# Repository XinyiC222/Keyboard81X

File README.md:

# Keyboard81X WORK IN PROGRESS

A custom 75% PCB keyboard with a rotary encoder and 81 keys.

## Build Notes

- PCB was designed in **KiCad** using a keyswitch plugin.
  - If you are trying to find it here are the ones I used:
    - **KLE Placer**  /Organize the keys and diodes automatically based on .json file
    - **JLCPCB tools** / used for BOM and Placement for JLC pcbs (**EDIT**: New version does not use JLCPCB assembly so this tool was no longer used in the final version. But this tool really do come in handy!)
- Case was modeled in **Fusion**.
## Tools I used
- Plate was generated with: <http://builder.swillkb.com/>
- Keyboard Layout Editor: <https://www.keyboard-layout-editor.com/>
- Keycaps used in the model: <https://github.com/anhthang/dsa-keycap>
- Footprint Library I used in Kicad: <https://github.com/daprice/keyswitches.pretty>

## How To Build Your Own! <h3>PCB</h3>

1. Build your layout with the layout editor I mentioned in the tools I used.
2. Download the .json file from there.
3. In KiCad schematics choose your microcontroller or just use a chip. I used a **Raspberry Pi Pico** for the final version and placed it under the space bar. Other option: you could use a RP2040 chip and build somewhat of a dev board inside the project. That includes the Flash Memory to store the code, Crystal Oscillator (it's like the conductor), USB for power with a voltage regulator, and some capacitors.
4. Then add the current amount of MX_SW_HS you need based on the layout you made.
5. Add the same amount of diodes so each key has one that includes any rotary encoders.
6. Then after that you can add some MX_Stab for the ones you want to stabilize. Some keys like the spacebar need stabilizers, so you can change them to different footprints from the other keys. If you decided to use plate mounted stabilizers instead, you can leave this part out, otherwise if you're using pcb mounted stabilizers then you should add MX_Stab.
7. Add footprint to all your components and don't forget to **Annotate the entire Schematics**
8. Now when designing the PCB, using the .json file and the KLE Placer plugin, you can easily place them all accordingly.
9. Remember to add a border around to create the edge of the PCB in the Edge.cut layer.
10. Organize all the components to your liking and route all of them to each other.
11. **Generate the Gerber Files!**
12. Then if you were to use JLCPCB assembly, you can use the JLCPCB tools to find all the components and create the correct BOM and CPL.
13. You can then upload those files into JLCPCB and order from there!!

<h3>Case</h3>

1. Go into Fusion and create a new project.
2. Download the 3D view of your keyboard from KiCad and upload it (for reference!)
3. Then make the case around it any way you like. If you are 3D printing remember that prints can shrink so you need to **account for tolerances especially holes**
4. you can add a plate and any type of mounting you want
5. If you are adding a plate, the plate generator I included above might be helpful
6. For the plate if you are 3D printing with PLA, having it at 1.5mm thick is usually not strong enough. Set it to **3mm** but leave the area around the stabilizers to be 1.5mm. Note that **prioritizing stability would cause your switches to not clip on correctly**, but will still be tight enough to hold them.

<h3>That's pretty much a good summary of how to build your own keyboard! Thanks for reading it and I hope you learned something new. This is my first big project and definitely my first keyboard build so I don't expect everything to be correct. So if you are building this based off of mine, it's not guaranteed to work. Have fun!!</h3>

## Schematics

## PCB

## BOM
Everything under quantity is the amount you need but the links you buy them come in bulk so they give you more than what you need.

| Item | Purpose | Price | Quantity | Source |
| --- | --- | --- | --- | --- |
| Raspberry Pi Pico | Mirco-controller | $1.99 | 1 | [Aliexpress](https://www.aliexpress.com/item/3256807207612469.html?spm=a2g0o.cart.0.0.6ac438dadamcUQ&mp=1&sourceType=570&pdp_npi=6%40dis%21USD%21USD%208.66%21USD%202.39%21%21USD%201.98%21%21%21%402101d3fe17861144495612456e0f9a%2112000040565295947%21ct%21US%217294405090%21%211%210%21&pdp_ext_f=%7B%22cart2PdpParams%22%3A%7B%22sourceType%22%3A%22570%22%2C%22cartSource%22%3A%22main%22%7D%7D) |
| 1N5817 DO-41 | USB_C VBUS | $1.79 | x1 | [Aliexpress](https://www.aliexpress.com/item/3256809192784213.html?spm=a2g0o.cart.0.0.6ac438dadamcUQ&mp=1&pdp_npi=6%40dis%21USD%21USD%203.83%21USD%201.92%21%21USD%201.92%21%21%21%402103119c17861142221435145e2191%2112000048926087942%21ct%21US%217294405090%21%211%210%21) |
| Keycaps | for the Keys | $4.73 | x80 | [Aliexpress](https://www.aliexpress.com/item/3256808108935624.html?spm=a2g0o.cart.0.0.6ac438dadamcUQ&mp=1&pdp_npi=6%40dis%21USD%21USD%204.73%21USD%204.73%21%21USD%204.73%21%21%21%402103119c17861142221435145e2191%2112000044523183095%21ct%21US%217294405090%21%211%210%21) |
| Plate Mounted Stabilizers | stab for space bar etc | $2.99 | has one 6.25u and two 2u | [Aliexpress](https://www.aliexpress.com/item/3256808467378574.html?spm=a2g0o.cart.0.0.6ac438dadamcUQ&mp=1&sourceType=570&pdp_npi=6%40dis%21USD%21USD%203.32%21USD%202.99%21%21USD%202.47%21%21%21%402101d3fe17861144495612456e0f9a%2112000046108045634%21ct%21US%217294405090%21%211%210%21&pdp_ext_f=%7B%22cart2PdpParams%22%3A%7B%22sourceType%22%3A%22570%22%2C%22cartSource%22%3A%22main%22%7D%7D) |
| SMD turtle switches | Reset button | $2.19 | x1 | [Aliexpress](https://www.aliexpress.com/item/3256805092773328.html?spm=a2g0o.cart.0.0.6ac438dadamcUQ&mp=1&sourceType=570&pdp_npi=6%40dis%21USD%21USD%202.25%21USD%202.19%21%21USD%201.81%21%21%21%402101d3fe17861144495612456e0f9a%2112000032466018228%21ct%21US%217294405090%21%211%210%21&pdp_ext_f=%7B%22cart2PdpParams%22%3A%7B%22sourceType%22%3A%22570%22%2C%22cartSource%22%3A%22main%22%7D%7D) |
| Hot Swap Sockets | hot swap keys | $6.20 | x80 | [Aliexpress](https://www.aliexpress.com/item/3256809001206372.html?spm=a2g0o.cart.0.0.6ac438dadamcUQ&mp=1&pdp_npi=6%40dis%21USD%21USD%2017.45%21USD%206.20%21%21USD%206.20%21%21%21%402101d3fe17861144435192279e0f9a%2112000048235529402%21ct%21US%217294405090%21%211%210%21) |
| Silent Axis switch | switches | $7.66 | x80 | [Aliexpress](https://www.aliexpress.com/item/3256812192263951.html?spm=a2g0o.cart.0.0.6ac438dadamcUQ&mp=1&pdp_npi=6%40dis%21USD%21USD%2018.05%21USD%207.66%21%21USD%207.66%21%21%21%402103119c17861142221435145e2191%2112000058235272628%21ct%21US%217294405090%21%211%210%21) |
| Type C Female | PCB for power | $2.24 | x1 | [Aliexpress](https://www.aliexpress.com/item/3256804989275660.html?spm=a2g0o.cart.0.0.6ac438dadamcUQ&mp=1&pdp_npi=6%40dis%21USD%21USD%202.27%21USD%202.26%21%21USD%202.26%21%21%21%402101d3fe17861144455232342e0f9a%2112000031972190842%21ct%21US%217294405090%21%211%210%21) |
| Solder | soldering | $2.14 | x1 | [Aliexpress](https://www.aliexpress.com/item/3256812349220377.html?spm=a2g0o.cart.0.0.6ac438dadamcUQ&mp=1&pdp_npi=6%40dis%21USD%21USD%204.45%21USD%202.14%21%21USD%202.14%21%21%21%402103119c17861142221435145e2191%2112000058646043574%21ct%21US%217294405090%21%211%210%21) |
| 5.1k resistors | for ground near usb-c | $2.48 | x2 | [Aliexpress](https://www.aliexpress.com/item/3256811592848349.html?spm=a2g0o.cart.0.0.6ac438dadamcUQ&mp=1&pdp_npi=6%40dis%21USD%21USD%203.01%21USD%202.42%21%21USD%202.42%21%21%21%402103119c17861142221435145e2191%2112000056534710480%21ct%21US%217294405090%21%211%210%21) |
| IN4148 DO-35 | matrix | $1.92 | x81 | [Aliexpress](https://www.aliexpress.com/item/3256809322506944.html?spm=a2g0o.cart.0.0.6ac438dadamcUQ&mp=1&sourceType=570&pdp_npi=6%40dis%21USD%21USD%203.81%21USD%201.79%21%21USD%201.22%21%21%21%402101d9ef17861148559937041e10b8%2112000049319061688%21ct%21US%217294405090%21%211%210%21&pdp_ext_f=%7B%22cart2PdpParams%22%3A%7B%22sourceType%22%3A%22570%22%2C%22cartSource%22%3A%22main%22%7D%7D) |
| Heat Inserts | To mount plate | $0.00 | 2 | Already Owned |
| M2.5 x 15mm bolts | Mount plate | $0.00 | 2 | Already Owned |
| Rotary Encoder | Volume knob | $0.00 | 1 | Already Owned |
| PCB | Connects everything | $39.36 | 1 | JLCPCB |
| 3D Prints | case for all the parts | $0.00 | | Printing Legion |
| Sub-Total+Tax |  | $37.48 |  | Aliexpress |
| Total |  | $76.84 |  | All Combined |

## Credits
<div align="center">

</div>

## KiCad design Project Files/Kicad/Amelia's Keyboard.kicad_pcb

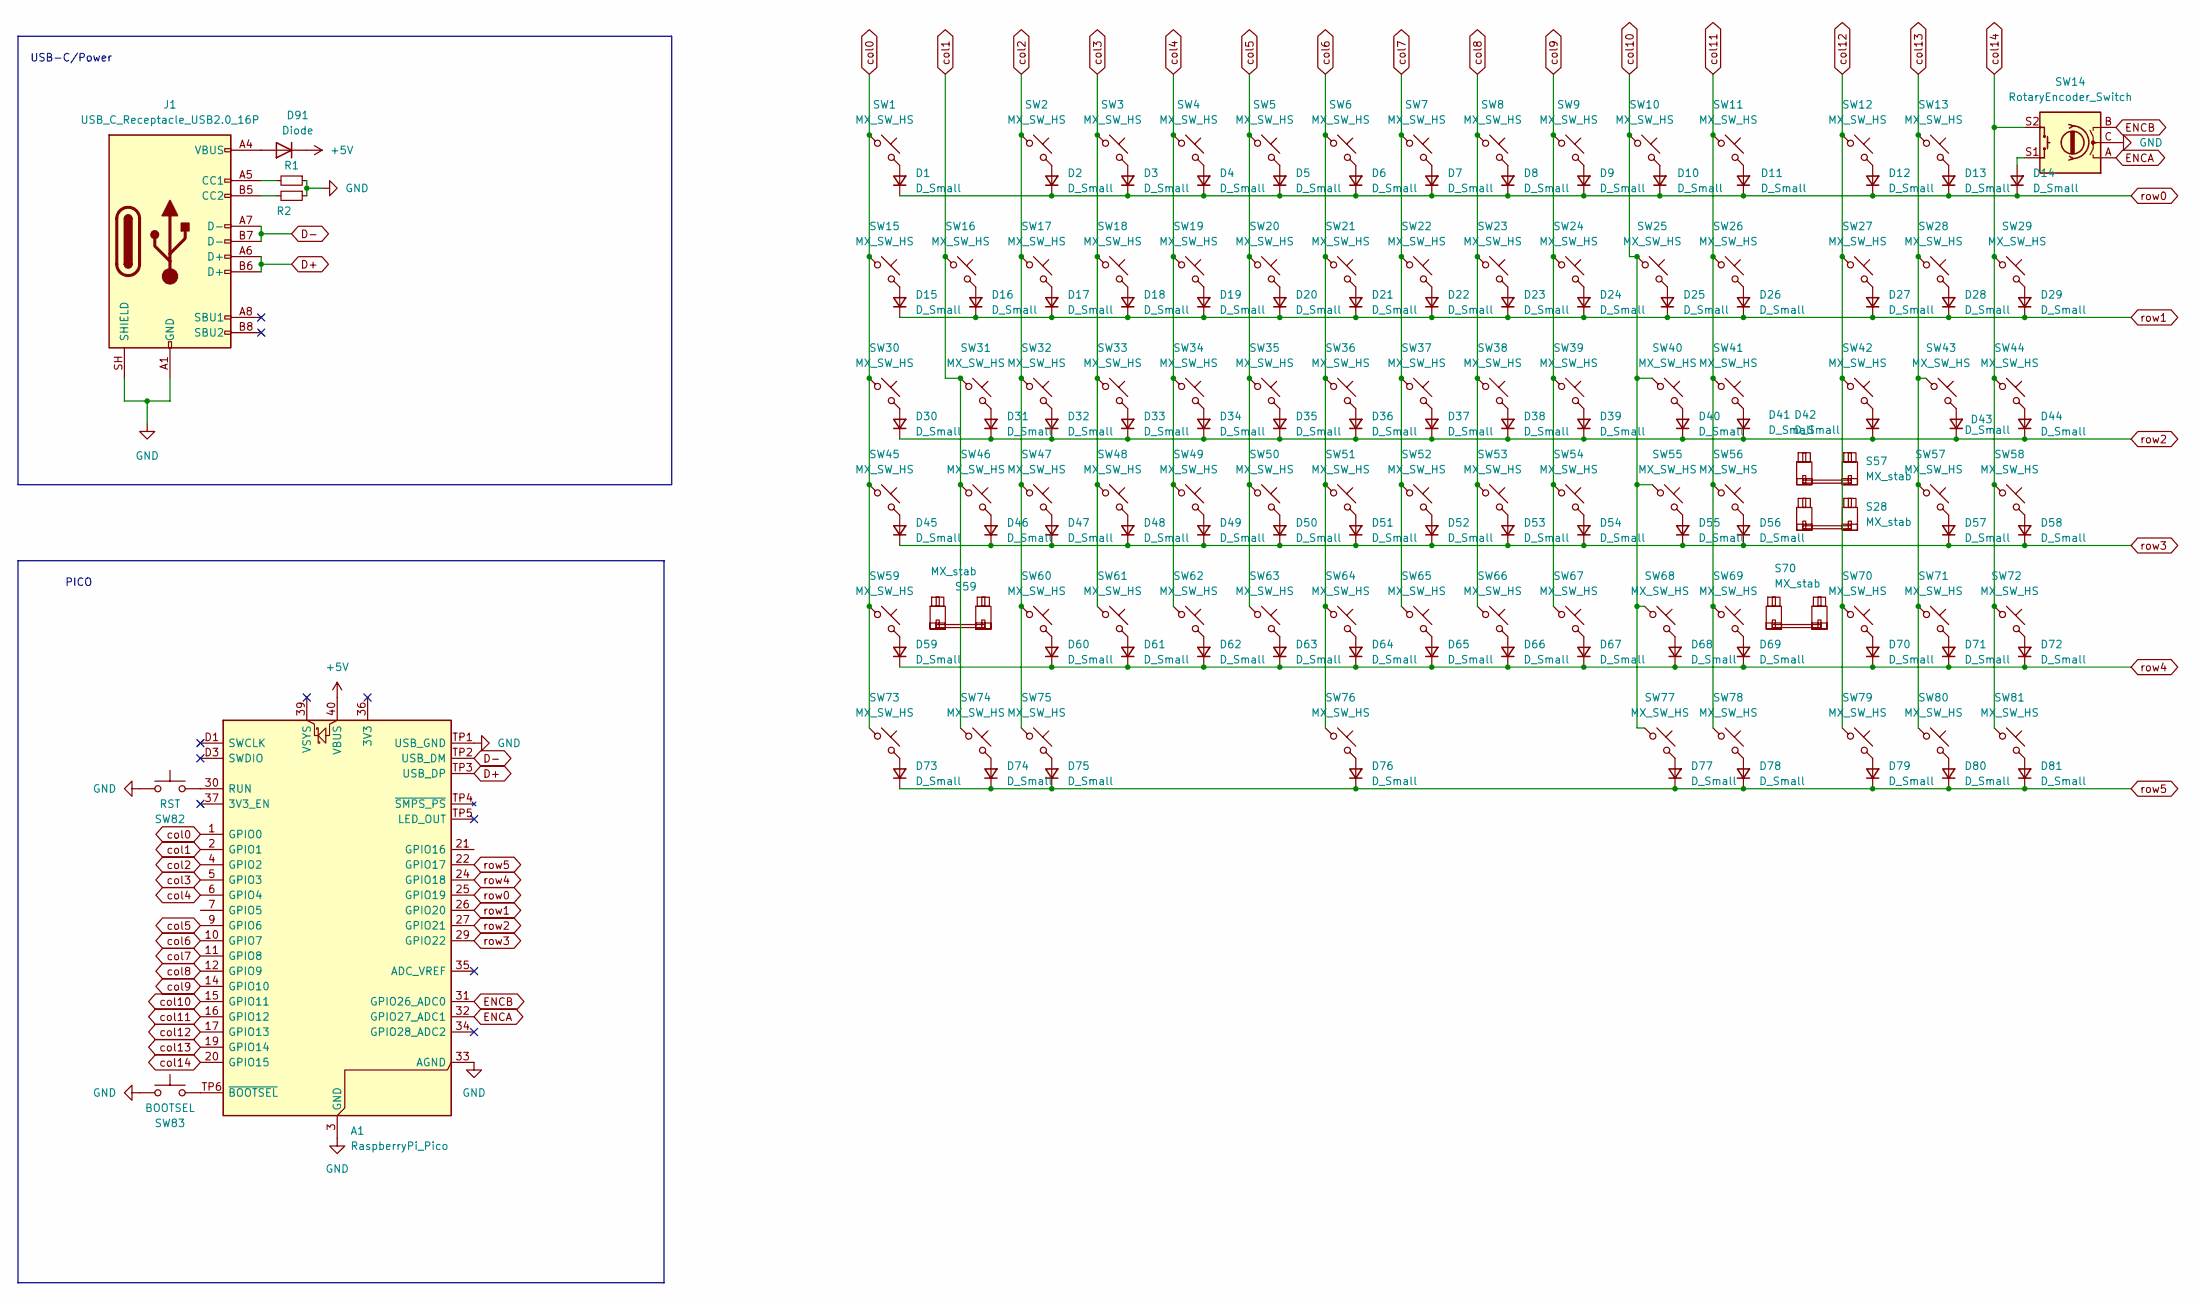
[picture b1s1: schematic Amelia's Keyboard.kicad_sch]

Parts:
A1: RaspberryPi_Pico; RaspberryPi_Pico_SMD
D1, D2, D3, D4, D5, D6, D7, D8, D9, D10, D11, D12, D13, D14, D15, D16, D17, D18, D19, D20, D21, D22, D23, D24, D25, D26, D27, D28, D29, D30, D31, D32, D33, D34, D35, D36, D37, D38, D39, D40, D41, D42, D43, D44, D45, D46, D47, D48, D49, D50, D51, D52, D53, D54, D55, D56, D57, D58, D59, D60, D61, D62, D63, D64, D65, D66, D67, D68, D69, D70, D71, D72, D73, D74, D75, D76, D77, D78, D79, D80, D81: D_Small; Diode_DO-35
D91: Diode; D_DO-41_SOD81_P7.62mm_Horizontal
J1: USB_C_Receptacle_USB2.0_16P; USB_C_Receptacle_HCTL_HC-TYPE-C-16P-01A
R1: R1; R_0805_2012Metric_Pad1.20x1.40mm_HandSolder
R2: R2; R_0805_2012Metric_Pad1.20x1.40mm_HandSolder
S28, S70: MX_stab; STAB_MX_P_2u
S57, S59: MX_stab; STAB_MX_P_2.25u
SW1, SW2, SW3, SW4, SW5, SW6, SW7, SW8, SW9, SW10, SW11, SW12, SW13, SW15, SW16, SW17, SW18, SW19, SW20, SW21, SW22, SW23, SW24, SW25, SW26, SW27, SW29, SW31, SW32, SW33, SW34, SW35, SW36, SW37, SW38, SW39, SW40, SW41, SW42, SW44, SW46, SW47, SW48, SW49, SW50, SW51, SW52, SW53, SW54, SW55, SW56, SW58, SW60, SW61, SW62, SW63, SW64, SW65, SW66, SW67, SW68, SW69, SW71, SW72, SW79, SW80, SW81: MX_SW_HS; SW_MX_HS_CPG151101S11_1u
SW14: RotaryEncoder_Switch; Encoder_EC11_MX
SW28, SW57: MX_SW_HS; SW_Hotswap_Kailh_MX_2.00u
SW30, SW43, SW75, SW77: MX_SW_HS; SW_MX_HS_CPG151101S11_1.5u
SW45, SW70: MX_SW_HS; SW_MX_HS_CPG151101S11_1.75u
SW59: MX_SW_HS; SW_Hotswap_Kailh_MX_2.25u
SW73, SW74, SW78: MX_SW_HS; SW_MX_HS_CPG151101S11_1.25u
SW76: MX_SW_HS; SW_Hotswap_Kailh_MX_6.25u
SW82: RST; SW_SPST_TS-1088-xR025
SW83: BOOTSEL; SW_SPST_TS-1088-xR025

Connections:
+5V: A1.40 (VBUS), D91.1 (K)
D+: A1.TP3 (USB_DP), J1.A6 (D+), J1.B6 (D+)
D-: A1.TP2 (USB_DM), J1.A7 (D-), J1.B7 (D-)
ENCA: A1.32 (GPIO27_ADC1), SW14.A
ENCB: A1.31 (GPIO26_ADC0), SW14.B
GND: A1.3 (GND), A1.8 (GND), A1.13 (GND), A1.18 (GND), A1.23 (GND), A1.28 (GND), A1.33 (AGND), A1.38 (GND), A1.D2 (GND), A1.TP1 (USB_GND), J1.A1 (GND), J1.A12 (GND), J1.B1 (GND), J1.B12 (GND), J1.SH (SHIELD), R1.1, R2.1, SW14.C, SW82.1, SW83.1
unnamed: A1.30 (RUN), SW82.2
unnamed: A1.TP6 (~BOOTSEL), SW83.2
unnamed: D1.2 (A), SW1.2
unnamed: D2.2 (A), SW2.2
unnamed: D3.2 (A), SW3.2
unnamed: D4.2 (A), SW4.2
unnamed: D5.2 (A), SW5.2
unnamed: D6.2 (A), SW6.2
unnamed: D7.2 (A), SW7.2
unnamed: D8.2 (A), SW8.2
unnamed: D9.2 (A), SW9.2
unnamed: D10.2 (A), SW10.2
unnamed: D11.2 (A), SW11.2
unnamed: D12.2 (A), SW12.2
unnamed: D13.2 (A), SW13.2
unnamed: D14.2 (A), SW14.S1
unnamed: D15.2 (A), SW15.2
unnamed: D16.2 (A), SW16.2
unnamed: D17.2 (A), SW17.2
unnamed: D18.2 (A), SW18.2
unnamed: D19.2 (A), SW19.2
unnamed: D20.2 (A), SW20.2
unnamed: D21.2 (A), SW21.2
unnamed: D22.2 (A), SW22.2
unnamed: D23.2 (A), SW23.2
unnamed: D24.2 (A), SW24.2
unnamed: D25.2 (A), SW25.2
unnamed: D26.2 (A), SW26.2
unnamed: D27.2 (A), SW27.2
unnamed: D28.2 (A), SW28.2
unnamed: D29.2 (A), SW29.2
unnamed: D30.2 (A), SW30.2
unnamed: D31.2 (A), SW31.2
unnamed: D32.2 (A), SW32.2
unnamed: D33.2 (A), SW33.2
unnamed: D34.2 (A), SW34.2
unnamed: D35.2 (A), SW35.2
unnamed: D36.2 (A), SW36.2
unnamed: D37.2 (A), SW37.2
unnamed: D38.2 (A), SW38.2
unnamed: D39.2 (A), SW39.2
unnamed: D40.2 (A), SW40.2
unnamed: D41.2 (A), SW41.2
unnamed: D42.2 (A), SW42.2
unnamed: D43.2 (A), SW43.2
unnamed: D44.2 (A), SW44.2
unnamed: D45.2 (A), SW45.2
unnamed: D46.2 (A), SW46.2
unnamed: D47.2 (A), SW47.2
unnamed: D48.2 (A), SW48.2
unnamed: D49.2 (A), SW49.2
unnamed: D50.2 (A), SW50.2
unnamed: D51.2 (A), SW51.2
unnamed: D52.2 (A), SW52.2
unnamed: D53.2 (A), SW53.2
unnamed: D54.2 (A), SW54.2
unnamed: D55.2 (A), SW55.2
unnamed: D56.2 (A), SW56.2
unnamed: D57.2 (A), SW57.2
unnamed: D58.2 (A), SW58.2
unnamed: D59.2 (A), SW59.2
unnamed: D60.2 (A), SW60.2
unnamed: D61.2 (A), SW61.2
unnamed: D62.2 (A), SW62.2
unnamed: D63.2 (A), SW63.2
unnamed: D64.2 (A), SW64.2
unnamed: D65.2 (A), SW65.2
unnamed: D66.2 (A), SW66.2
unnamed: D67.2 (A), SW67.2
unnamed: D68.2 (A), SW68.2
unnamed: D69.2 (A), SW69.2
unnamed: D70.2 (A), SW70.2
unnamed: D71.2 (A), SW71.2
unnamed: D72.2 (A), SW72.2
unnamed: D73.2 (A), SW73.2
unnamed: D74.2 (A), SW74.2
unnamed: D75.2 (A), SW75.2
unnamed: D76.2 (A), SW76.2
unnamed: D77.2 (A), SW77.2
unnamed: D78.2 (A), SW78.2
unnamed: D79.2 (A), SW79.2
unnamed: D80.2 (A), SW80.2
unnamed: D81.2 (A), SW81.2
unnamed: D91.2 (A), J1.A4 (VBUS), J1.A9 (VBUS), J1.B4 (VBUS), J1.B9 (VBUS)
unnamed: J1.A5 (CC1), R1.2
unnamed: J1.B5 (CC2), R2.2
col0: A1.1 (GPIO0), SW1.1, SW15.1, SW30.1, SW45.1, SW59.1, SW73.1
col1: A1.2 (GPIO1), SW16.1, SW31.1, SW46.1, SW74.1
col2: A1.4 (GPIO2), SW2.1, SW17.1, SW32.1, SW47.1, SW60.1, SW75.1
col3: A1.5 (GPIO3), SW3.1, SW18.1, SW33.1, SW48.1, SW61.1
col4: A1.6 (GPIO4), SW4.1, SW19.1, SW34.1, SW49.1, SW62.1
col5: A1.9 (GPIO6), SW5.1, SW20.1, SW35.1, SW50.1, SW63.1
col6: A1.10 (GPIO7), SW6.1, SW21.1, SW36.1, SW51.1, SW64.1, SW76.1
col7: A1.11 (GPIO8), SW7.1, SW22.1, SW37.1, SW52.1, SW65.1
col8: A1.12 (GPIO9), SW8.1, SW23.1, SW38.1, SW53.1, SW66.1
col9: A1.14 (GPIO10), SW9.1, SW24.1, SW39.1, SW54.1, SW67.1
col10: A1.15 (GPIO11), SW10.1, SW25.1, SW40.1, SW55.1, SW68.1, SW77.1
col11: A1.16 (GPIO12), SW11.1, SW26.1, SW41.1, SW56.1, SW69.1, SW78.1
col12: A1.17 (GPIO13), SW12.1, SW27.1, SW42.1, SW70.1, SW79.1
col13: A1.19 (GPIO14), SW13.1, SW28.1, SW43.1, SW57.1, SW71.1, SW80.1
col14: A1.20 (GPIO15), SW14.S2, SW29.1, SW44.1, SW58.1, SW72.1, SW81.1
row0: A1.25 (GPIO19), D1.1 (K), D2.1 (K), D3.1 (K), D4.1 (K), D5.1 (K), D6.1 (K), D7.1 (K), D8.1 (K), D9.1 (K), D10.1 (K), D11.1 (K), D12.1 (K), D13.1 (K), D14.1 (K)
row1: A1.26 (GPIO20), D15.1 (K), D16.1 (K), D17.1 (K), D18.1 (K), D19.1 (K), D20.1 (K), D21.1 (K), D22.1 (K), D23.1 (K), D24.1 (K), D25.1 (K), D26.1 (K), D27.1 (K), D28.1 (K), D29.1 (K)
row2: A1.27 (GPIO21), D30.1 (K), D31.1 (K), D32.1 (K), D33.1 (K), D34.1 (K), D35.1 (K), D36.1 (K), D37.1 (K), D38.1 (K), D39.1 (K), D40.1 (K), D41.1 (K), D42.1 (K), D43.1 (K), D44.1 (K)
row3: A1.29 (GPIO22), D45.1 (K), D46.1 (K), D47.1 (K), D48.1 (K), D49.1 (K), D50.1 (K), D51.1 (K), D52.1 (K), D53.1 (K), D54.1 (K), D55.1 (K), D56.1 (K), D57.1 (K), D58.1 (K)
row4: A1.24 (GPIO18), D59.1 (K), D60.1 (K), D61.1 (K), D62.1 (K), D63.1 (K), D64.1 (K), D65.1 (K), D66.1 (K), D67.1 (K), D68.1 (K), D69.1 (K), D70.1 (K), D71.1 (K), D72.1 (K)
row5: A1.22 (GPIO17), D73.1 (K), D74.1 (K), D75.1 (K), D76.1 (K), D77.1 (K), D78.1 (K), D79.1 (K), D80.1 (K), D81.1 (K)

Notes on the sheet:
USB-C/Power
PICO

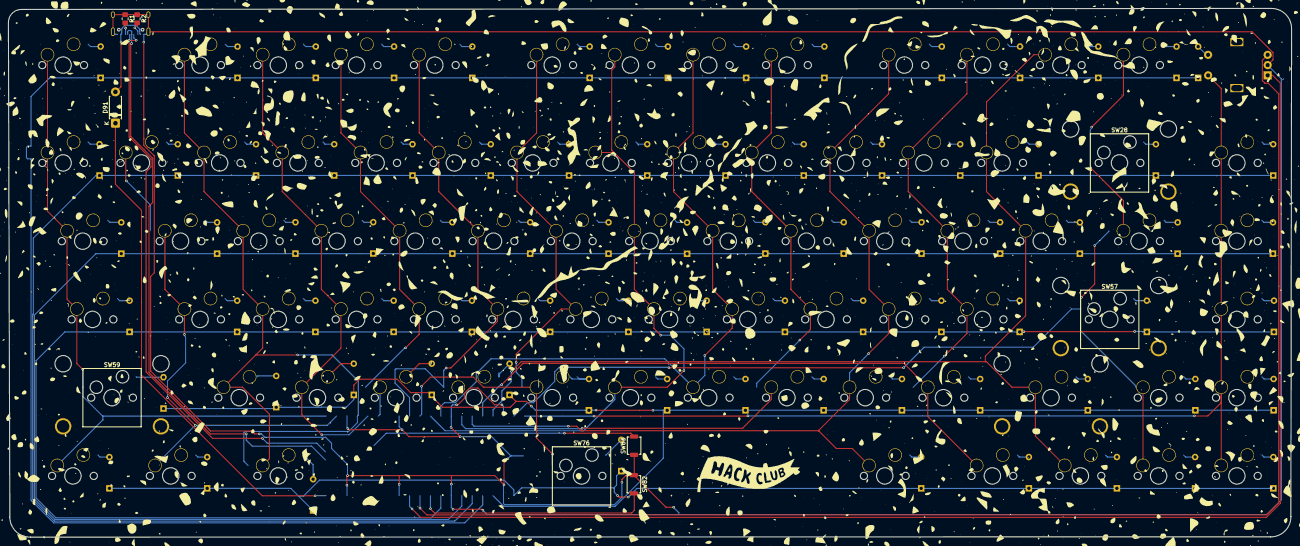
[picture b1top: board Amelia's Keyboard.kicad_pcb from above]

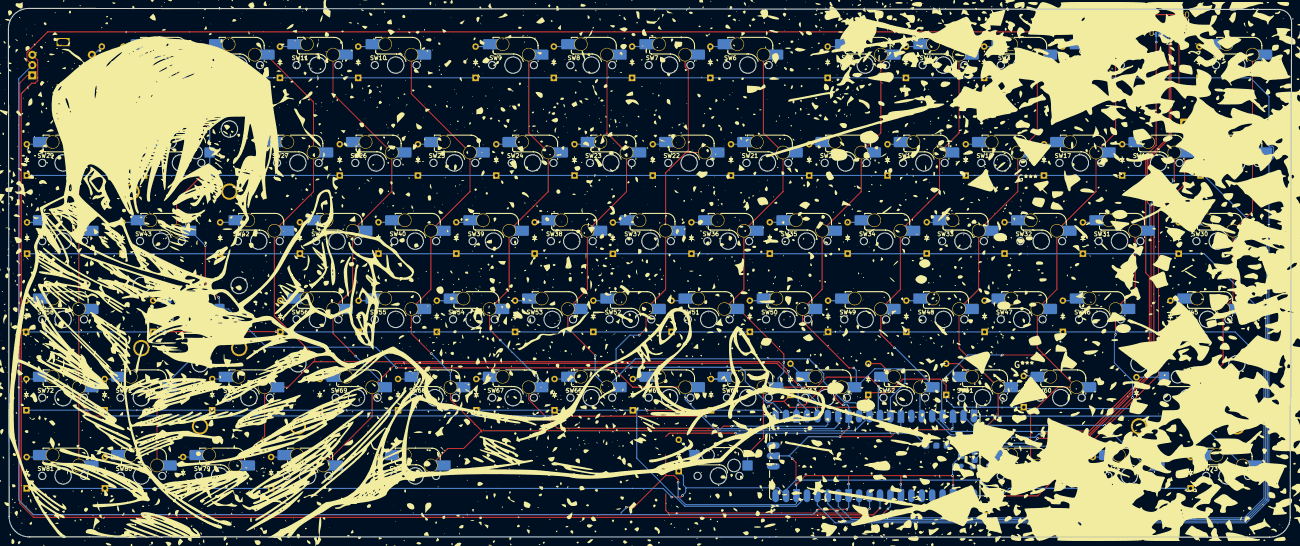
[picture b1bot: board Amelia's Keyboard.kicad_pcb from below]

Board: 2 copper layers, 312.4 x 128.7 mm, 173 parts (163 on the bottom side), 113 nets.
